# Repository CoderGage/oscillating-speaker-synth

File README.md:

# Oscillating Speaker Synth
## A PCB design that creates a synth-like sound with an oscillating circuit.

I wanted to create something like a Stylophone that creates a synth sound, but with a simple circuit embedded in a PCB, with only pitch and volume control. I figured I could create some interesting sounds and play around with making multiple of them. I plan to expand on this project with more synth controllers, but I want to start with this one to get a basic understanding of synth circuits, PCB design, and Hack Club's YSWS opportunities.

## Bill of Materials
| 10 uf capacitor | HAVE |
| 100 uf capacitor | HAVE |
| Barrel jack | Ordering from Adafruit (https://www.adafruit.com/product/373) |
| Speaker terminal block | Ordering from Adafruit (https://www.adafruit.com/product/724) |
| Transistors | HAVE |
| All resistors | HAVE |
| Potentiometers (variable resistors) | Ordering from Adafruit (https://www.adafruit.com/product/5277) and (https://www.adafruit.com/product/5282) |
| SPST Switch | Ordering from Adafruit (https://www.adafruit.com/product/3221) |

## Original project diagram

## PCB schematic

## PCB component placement

## PCB 3d render with components

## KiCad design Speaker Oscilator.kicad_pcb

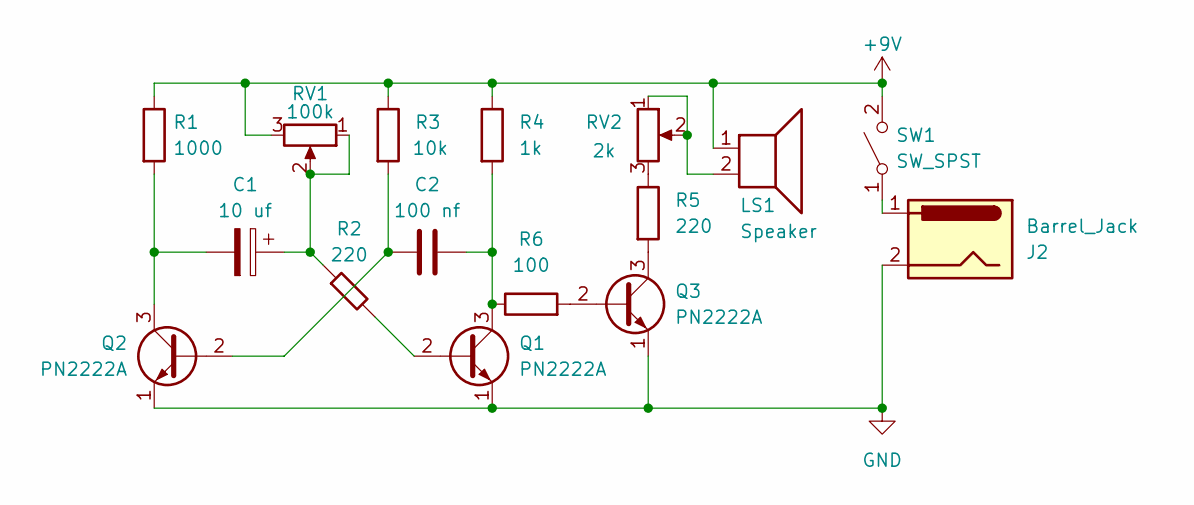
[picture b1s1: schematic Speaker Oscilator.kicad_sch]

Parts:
C1: 10 uf; CP_Radial_D8.0mm_P5.00mm
C2: 100 nf; C_Disc_D5.0mm_W2.5mm_P5.00mm
J2: Barrel_Jack; BarrelJack_Horizontal
LS1: Speaker; TerminalBlock_4Ucon_1x02_P3.50mm_Horizontal
Q1, Q2, Q3: PN2222A; TO-92_Inline_Wide
R1: 1000; R_Axial_DIN0207_L6.3mm_D2.5mm_P7.62mm_Horizontal
R2, R5: 220; R_Axial_DIN0207_L6.3mm_D2.5mm_P7.62mm_Horizontal
R3: 10k; R_Axial_DIN0207_L6.3mm_D2.5mm_P7.62mm_Horizontal
R4: 1k; R_Axial_DIN0207_L6.3mm_D2.5mm_P7.62mm_Horizontal
R6: 100; R_Axial_DIN0207_L6.3mm_D2.5mm_P7.62mm_Horizontal
RV1: 100k; Potentiometer_Bourns_PTV09A-1_Single_Vertical
RV2: 2k; Potentiometer_Bourns_PTV09A-1_Single_Vertical
SW1: SW_SPST; SW_DIP_SPSTx01_Slide_6.7x4.1mm_W7.62mm_P2.54mm_LowProfile

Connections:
+9V: LS1.1, R1.1, R3.1, R4.1, RV1.3, SW1.2 (B)
GND: J2.2, Q1.1 (E), Q2.1 (E), Q3.1 (E)
unnamed: C1.1, R2.1, RV1.1, RV1.2
unnamed: LS1.2, RV2.1, RV2.2
unnamed: Q1.2 (B), R2.2
unnamed: C2.2, Q1.3 (C), R4.2, R6.1
unnamed: C2.1, Q2.2 (B), R3.2
unnamed: C1.2, Q2.3 (C), R1.2
unnamed: Q3.2 (B), R6.2
unnamed: Q3.3 (C), R5.2
unnamed: R5.1, RV2.3
unnamed: J2.1, SW1.1 (A)

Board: 2 copper layers, 16 parts (0 on the bottom side), 12 nets, no tracks yet.

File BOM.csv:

"Reference","Qty","Value","DNP","Exclude from BOM","Exclude from Board","Footprint","Datasheet"
"C1","1","10 uf","","","","Capacitor_THT:CP_Axial_L10.0mm_D4.5mm_P15.00mm_Horizontal",""
"C2","1","100 nf","","","","Capacitor_THT:C_Disc_D3.0mm_W2.0mm_P2.50mm",""
"J2","1","Barrel_Jack","","","","Connector_BarrelJack:BarrelJack_Horizontal",""
"LS1","1","Speaker","","","","TerminalBlock:TerminalBlock_MaiXu_MX126-5.0-02P_1x02_P5.00mm",""
"Q1,Q2,Q3","3","PN2222A","","","","Package_TO_SOT_THT:TO-92_Inline","https://www.onsemi.com/pub/Collateral/PN2222-D.PDF"
"R1","1","1000","","","","Resistor_SMD:R_01005_0402Metric",""
"R2,R5","2","220","","","","Resistor_SMD:R_01005_0402Metric",""
"R3","1","10k","","","","Resistor_SMD:R_01005_0402Metric",""
"R4","1","1k","","","","Resistor_SMD:R_01005_0402Metric",""
"R6","1","100","","","","Resistor_SMD:R_01005_0402Metric",""
"RV1","1","100k","","","","Potentiometer_THT:Potentiometer_ACP_CA14V-15_Vertical",""
"RV2","1","2k","","","","Potentiometer_THT:Potentiometer_ACP_CA14V-15_Vertical",""
"SW1","1","SW_SPST","","","","Button_Switch_THT:SW_DIP_SPSTx01_Slide_6.7x4.1mm_W7.62mm_P2.54mm_LowProfile",""

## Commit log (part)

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2026-06-27 Uploaded BOM, PCB file, and schematic file
2026-06-27 Added project description to README
    Expanded project description and improved formatting.
2026-06-27 Added project photos to README
    Added images for project diagram, PCB schematic, component placement, and 3D render.
2026-06-27 Add Bill of Materials to README
    Added a Bill of Materials section with components and ordering information.
2026-06-27 Refactor Bill of Materials to table format
    Updated the Bill of Materials section to use a table format for better readability.
